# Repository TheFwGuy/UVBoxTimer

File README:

UV Box Timer project

To compile, Set Energia to have the library included and open UVBoxTimer.ino.

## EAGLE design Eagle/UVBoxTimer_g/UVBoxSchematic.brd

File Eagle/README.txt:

The original schematic is under UVBoxTimer.
UVBoxTimer_g is the one created by Roberto in order to prepare the PCB.
So the PCB related schematic is under UVBoxTimer_g, and the schematic is named UVBoxSchematic_r.sch

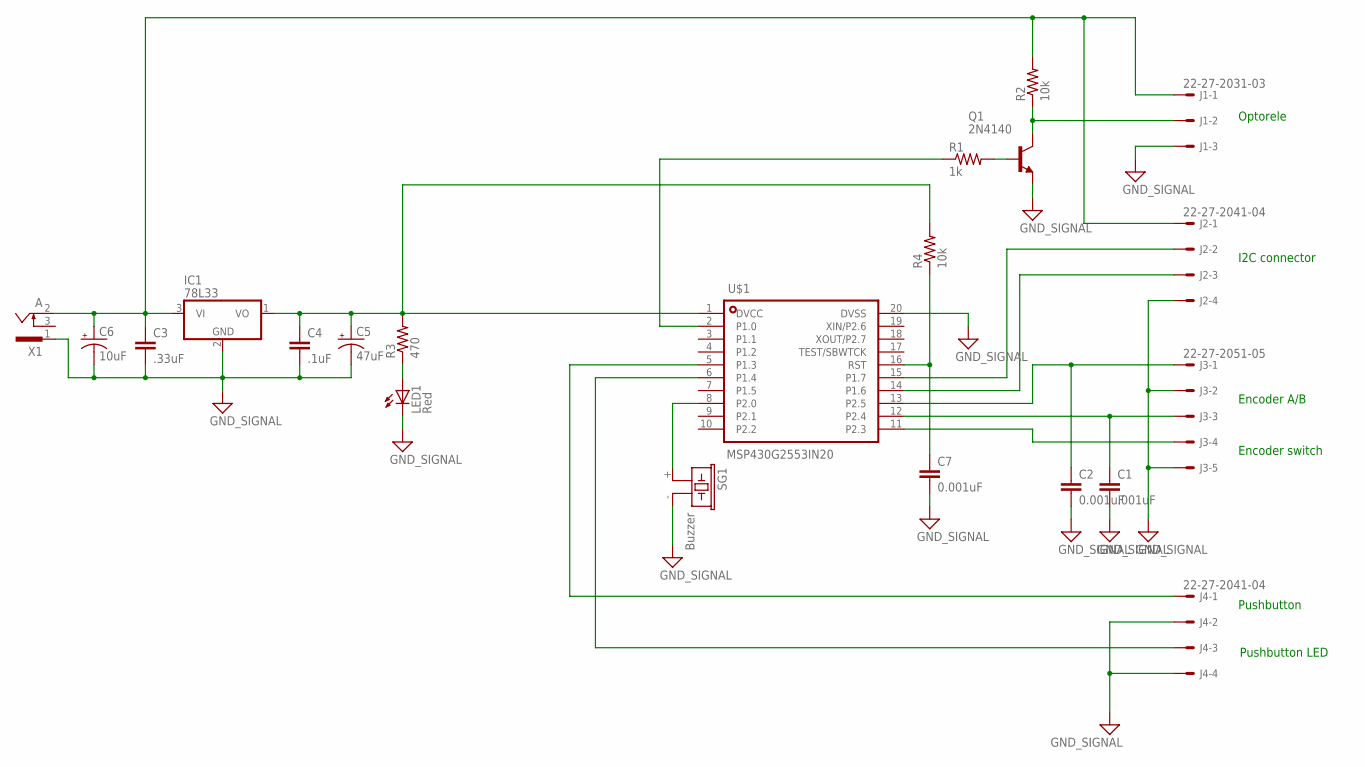
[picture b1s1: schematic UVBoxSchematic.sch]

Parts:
C1: .001uF; C5B3
C2, C7: 0.001uF; C5B3
C3: .33uF; C5B3
C4: .1uF; C5B3
C5: 47uF; B45181A
C6: 10uF; B45181A
IC1: 78L33; TO92
J1: 22-27-2031-03; 6410-03
J2, J4: 22-27-2041-04; 6410-04
J3: 22-27-2051-05; 6410-05
LED1: Red; LED3MM
Q1: 2N4140; TO18
R1: 1k; 0204/7
R2, R4: 10k; 0204/7
R3: 470; 0204/7
SG1: Buzzer; F/CM04P
U$1: MSP430G2553IN20; DIP20
X1: A; SCD-014-A

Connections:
GND: C1.2, C2.2, C3.2, C4.2, C5.-, C6.-, C7.2, IC1.2 (GND), J1.3, J2.4, J3.2, J3.5, J4.2, J4.4, LED1.K (C), Q1.1 (E), SG1.- (2), U$1.20 (DVSS), X1.1
unnamed: C3.1, C6.+, IC1.3 (VI), J1.1, J2.1, R2.2, X1.2
unnamed: C2.1, J3.1, U$1.13 (P2.5)
unnamed: C1.1, J3.3, U$1.12 (P2.4)
unnamed: J3.4, U$1.11 (P2.3)
unnamed: J2.3, U$1.14 (P1.6)
unnamed: J2.2, U$1.15 (P1.7)
unnamed: LED1.A, R3.1
unnamed: C4.1, C5.+, IC1.1 (VO), R3.2, R4.2, U$1.1 (DVCC)
unnamed: J4.1, U$1.5 (P1.3)
unnamed: J1.2, Q1.3 (C), R2.1
unnamed: Q1.2 (B), R1.2
unnamed: R1.1, U$1.2 (P1.0)
unnamed: J4.3, U$1.6 (P1.4)
unnamed: SG1.+ (1), U$1.8 (P2.0)
unnamed: C7.1, R4.1, U$1.16 (RST)

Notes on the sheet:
Encoder A/B
Encoder switch
I2C connector
Optorele
Pushbutton
Pushbutton LED

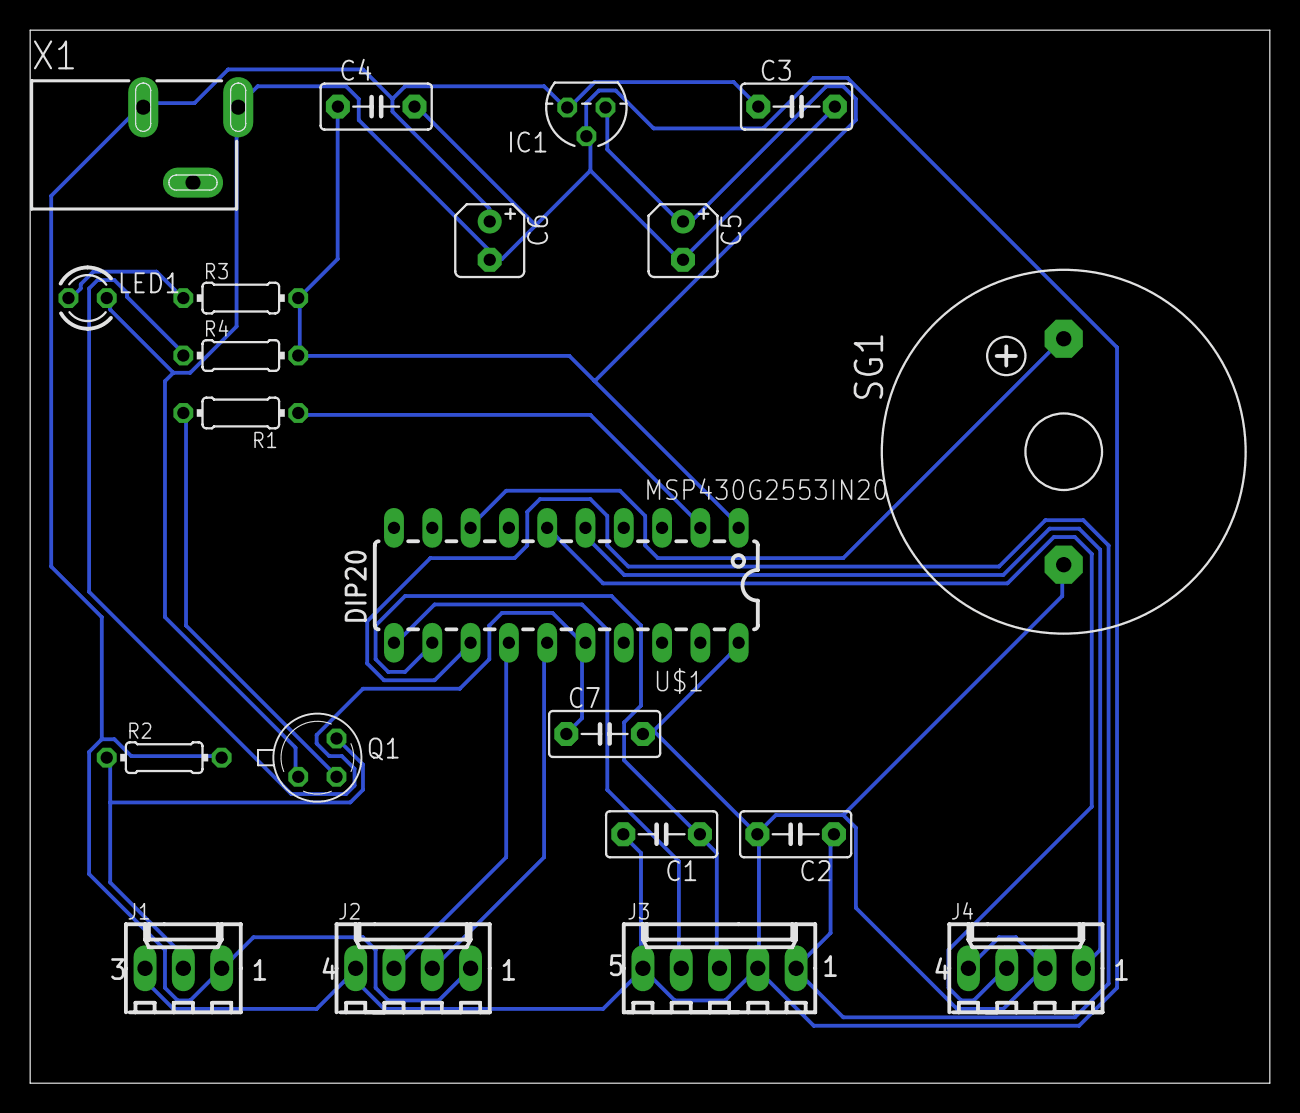
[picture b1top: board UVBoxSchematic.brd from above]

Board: 2 copper layers, 82.2 x 69.8 mm, 21 parts (0 on the bottom side), 16 nets.

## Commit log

2015-11-12 Added schematics
2015-11-12 Selected I2C mode - little bit clean up
2015-11-12 Removed pull ups - are set in the pin
2015-11-12 Cleaned up the code - rewriting code - added state amchine
2015-11-13 Renamed from README - added library info
2015-11-13 Restored lcd.print(value)
2015-11-13 removed libraries
2015-11-13 Removed sprintf - replaced with lcd.print(value)
2015-11-13 set increment of 5 - prevented change param during run
2015-11-13 Added conversion time function - not debugged
2015-11-14 Fixed encoder/pushbutton reading - changed messages - other fixing
2015-11-14 Changed menu' - display - UI interface - big enhancements - fixed encoder-pushbutton readings
2015-11-17 Added Pushbutton LED management
2015-11-17 Added 2 .001uF capacitor for encoder
2015-11-17 Added relays
2015-11-24 Adding buzzer - porting out SpiByWire - minor adjustments
2015-11-24 Added functionalities
2015-11-24 Added buzzer I/O
2015-11-24 Added gitignore to exclude dia old
2015-11-24 Diagramas updated
2015-11-24 Revisited states machine
2015-11-25 Optimized state machine
2015-11-25 Correction to state machine
2015-11-25 Correction pinout
2015-11-28 Changed management for different encoder
2015-11-28 Presets
2015-11-30 start flow new state machine
2015-12-01 Flow for setting menu
2015-12-01 update schematic to latest tests
2015-12-01 Updated for the latest menu selection
2015-12-01 Modifying for menu selection - not complete
2015-12-04 Change heavily management to add presets and other improvements
2017-09-19 Added Eagle schematics
2017-09-19 Changed eagle version
2017-09-19 Added note
2017-09-20 Removed duplicate schematics
